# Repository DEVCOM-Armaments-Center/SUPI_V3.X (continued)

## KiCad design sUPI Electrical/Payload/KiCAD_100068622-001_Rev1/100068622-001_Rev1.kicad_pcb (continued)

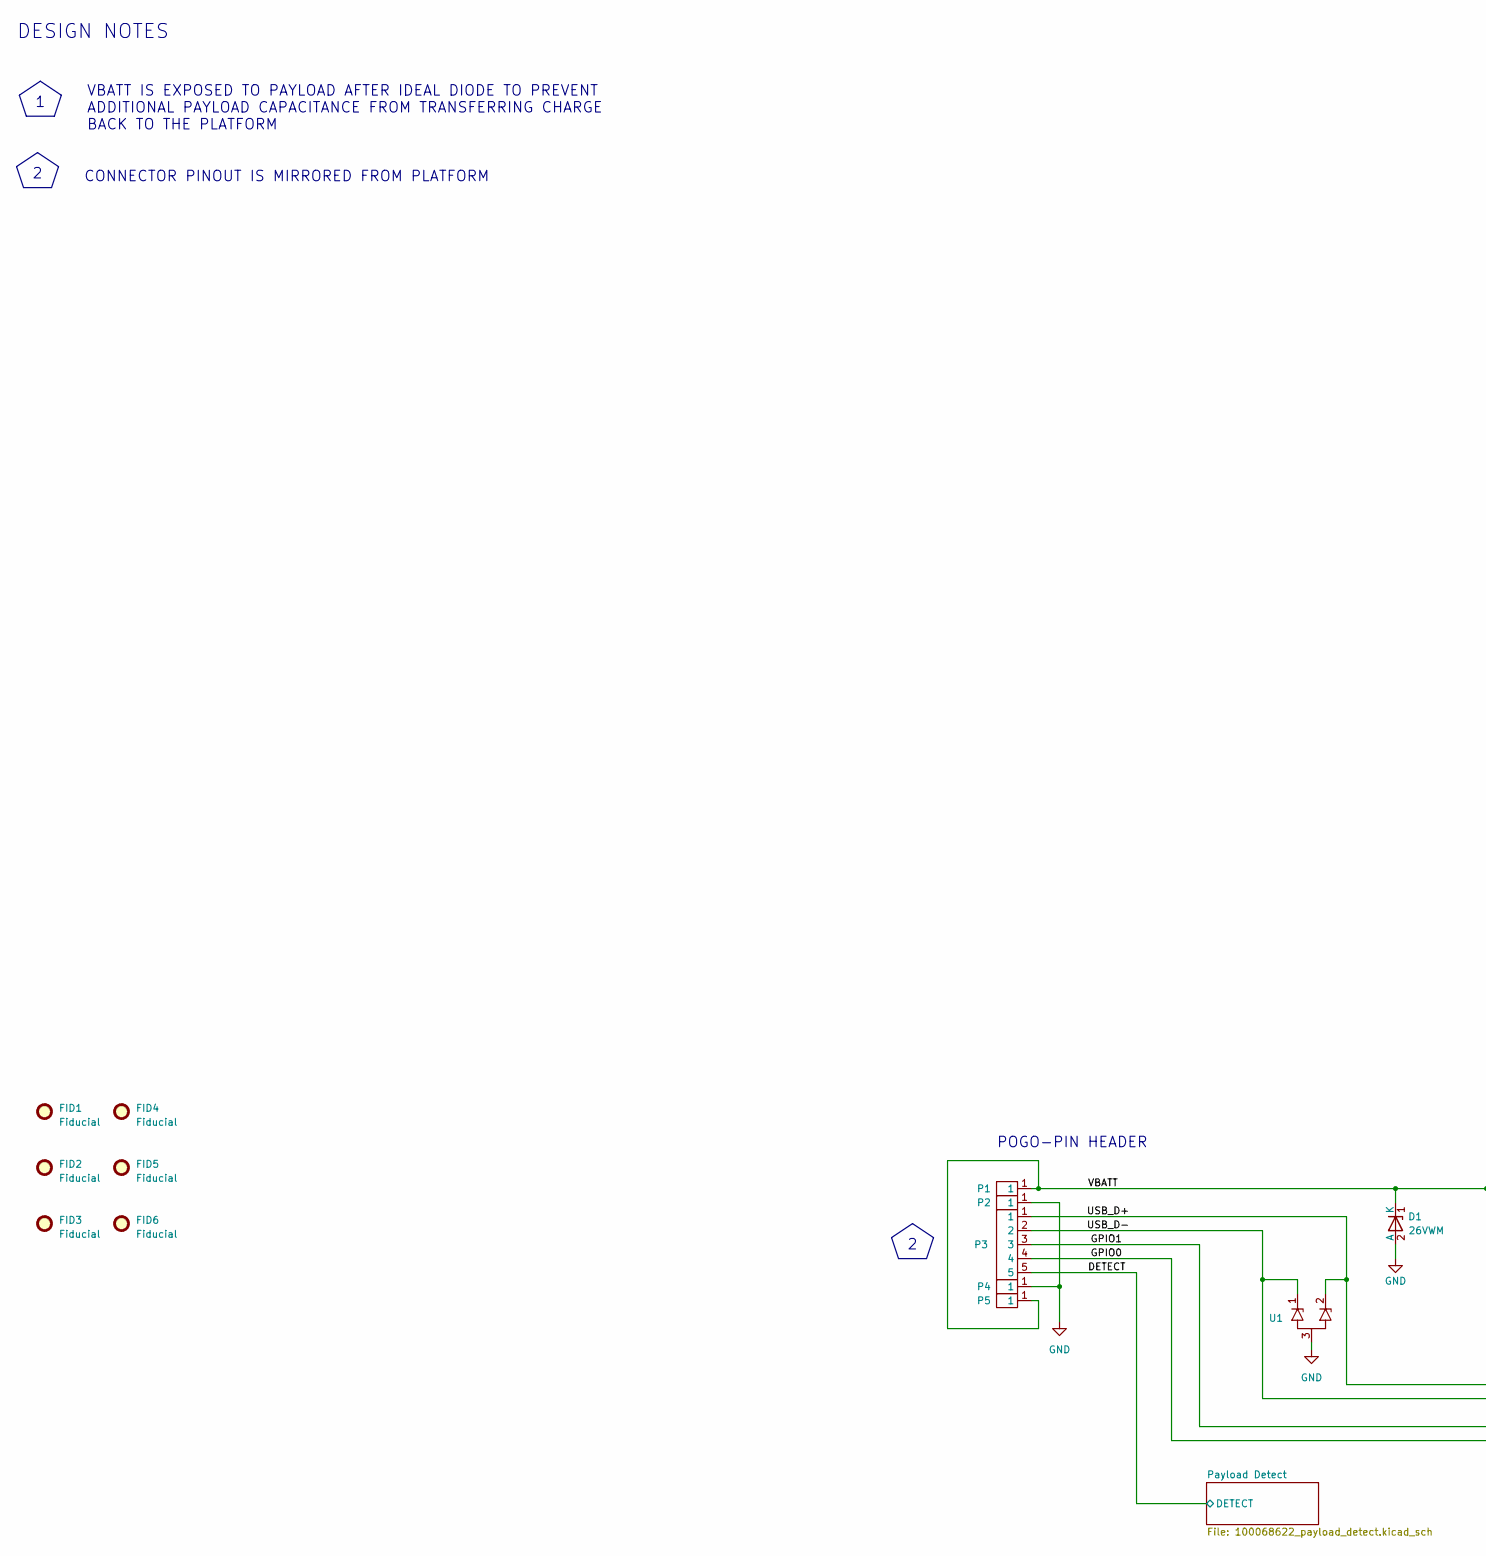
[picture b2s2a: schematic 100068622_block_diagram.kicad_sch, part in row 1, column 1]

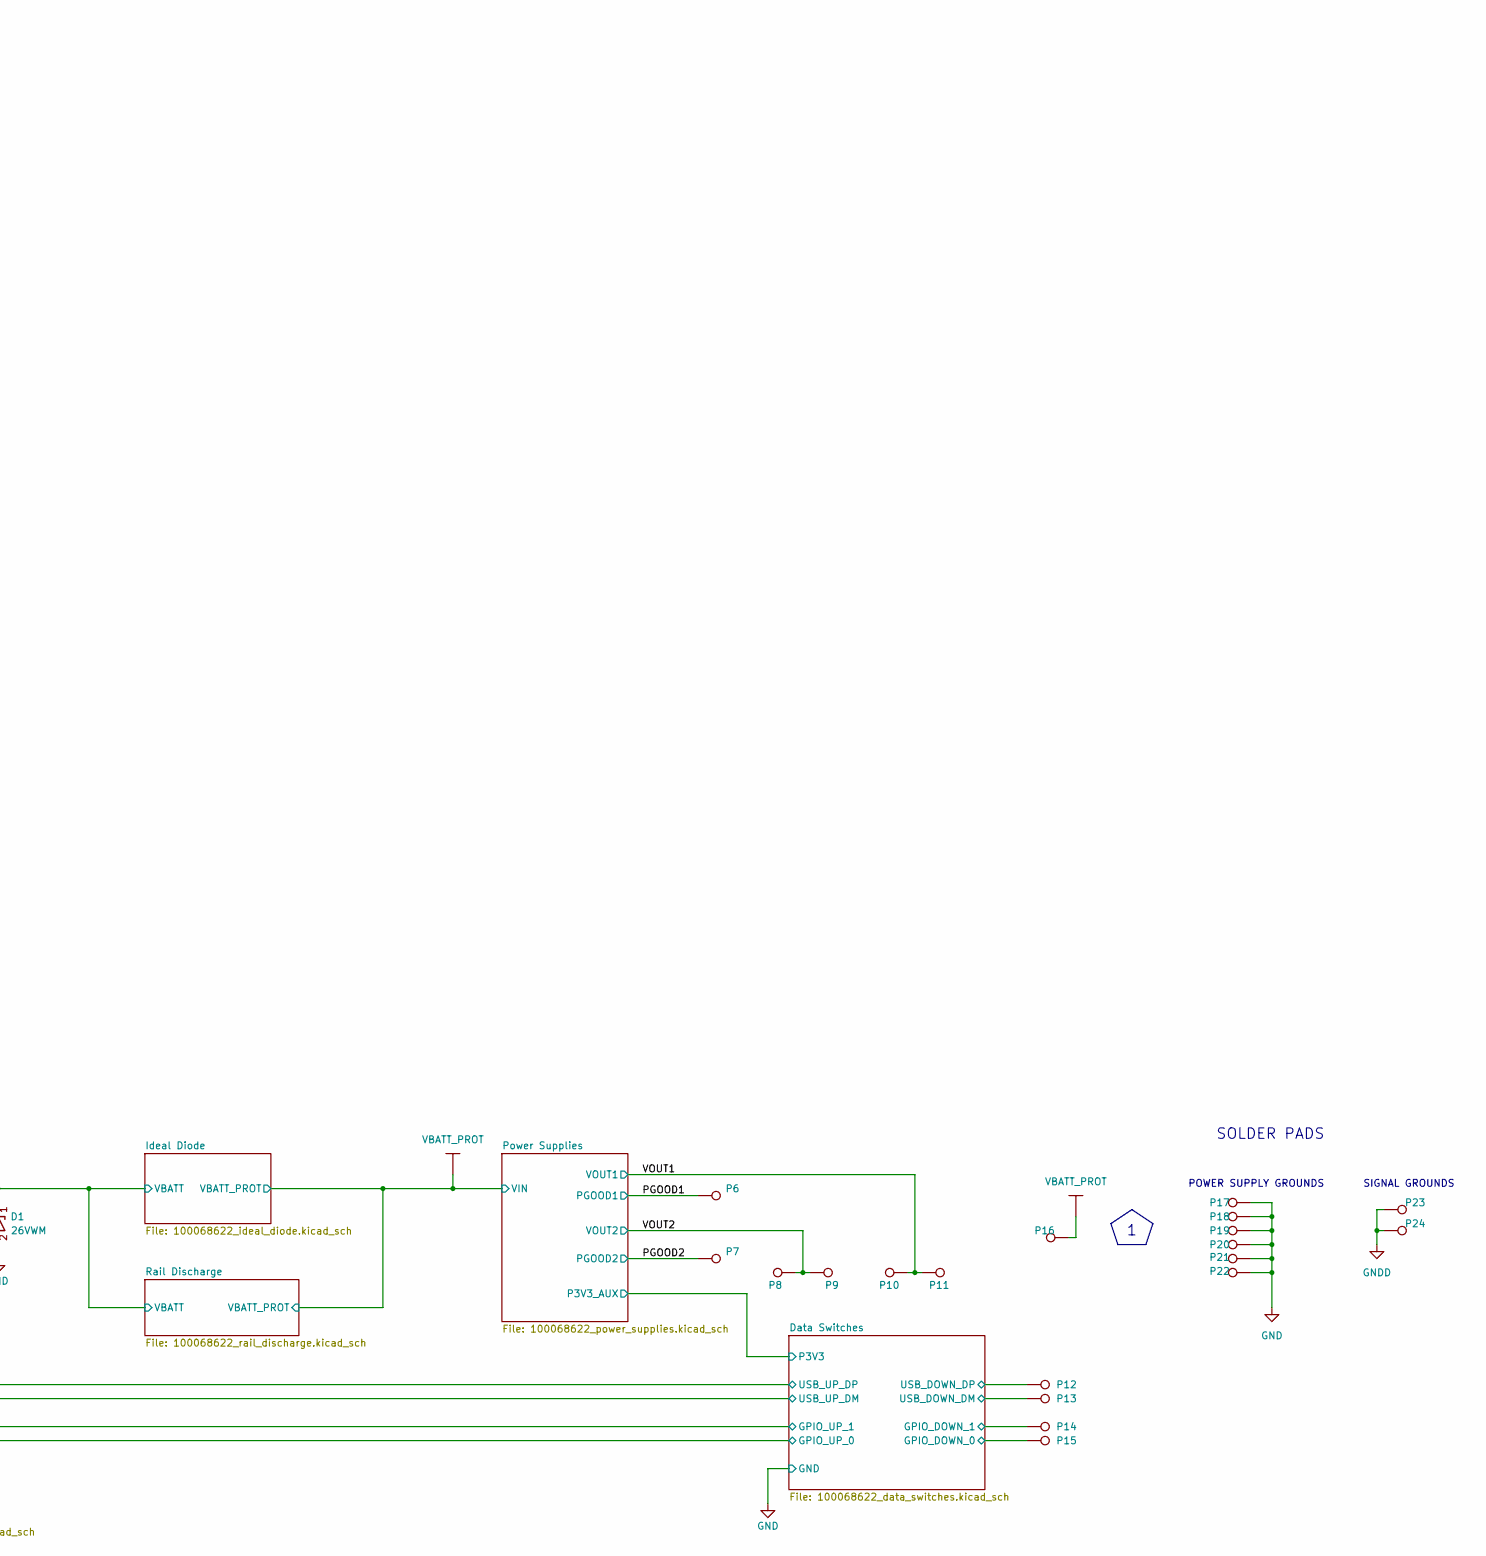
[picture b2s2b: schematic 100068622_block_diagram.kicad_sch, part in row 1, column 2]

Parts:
D1: 26VWM; SOD-123FL; MPN SMF26A
FID1, FID2, FID3, FID4, FID5, FID6: Fiducial; Fiducial_Cu0.040_Mask0.060
P1, P5: 829-22-001-20-001101; MPN 829-22-001-20-001101
P2, P4: 829-22-001-20-002101; MPN 829-22-001-20-002101
P3: 829-22-005-20-001101; MPN 829-22-005-20-001101
P6, P7, P8, P9, P10, P11, P12, P13, P14, P15, P17, P18, P19, P20, P21, P23, P24: Hand_Solder_Pad_100x80_mil
P16, P22: Hand_Solder_Pad_200x150_mil
U1: Diodes_DFN1006-3; MPN PESD5V0C2UM

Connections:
/Block Diagram/DETECT: P3.5; also elsewhere on the board
/Block Diagram/Data Switches/GPIO_DOWN_0: P15.1; also elsewhere on the board
/Block Diagram/Data Switches/GPIO_DOWN_1: P14.1; also elsewhere on the board
/Block Diagram/Data Switches/USB_DOWN_DM: P13.1; also elsewhere on the board
/Block Diagram/Data Switches/USB_DOWN_DP: P12.1; also elsewhere on the board
/Block Diagram/GPIO0: P3.4; also elsewhere on the board
/Block Diagram/GPIO1: P3.3; also elsewhere on the board
/Block Diagram/PGOOD1: P6.1; also elsewhere on the board
/Block Diagram/PGOOD2: P7.1; also elsewhere on the board
/Block Diagram/USB_D+: P3.1, U1.2 (K2); also elsewhere on the board
/Block Diagram/USB_D-: P3.2, U1.1 (K1); also elsewhere on the board
/Block Diagram/VBATT: D1.1 (K), P1.1, P5.1; also elsewhere on the board
/Block Diagram/VOUT1: P10.1, P11.1; also elsewhere on the board
/Block Diagram/VOUT2: P8.1, P9.1; also elsewhere on the board
GND: D1.2 (A), P2.1, P4.1, P17.1, P18.1, P19.1, P20.1, P21.1, P22.1, U1.3 (A); also elsewhere on the board
GNDD: P23.1, P24.1; also elsewhere on the board
VBATT_PROT: P16.1; also elsewhere on the board

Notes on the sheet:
CONNECTOR PINOUT IS MIRRORED FROM PLATFORM
POGO-PIN HEADER
SOLDER PADS
DESIGN NOTES
SIGNAL GROUNDS
POWER SUPPLY GROUNDS
VBATT IS EXPOSED TO PAYLOAD AFTER IDEAL DIODE TO PREVENT ADDITIONAL PAYLOAD CAPACITANCE FROM TRANSFERRING CHARGE BACK TO THE PLATFORM

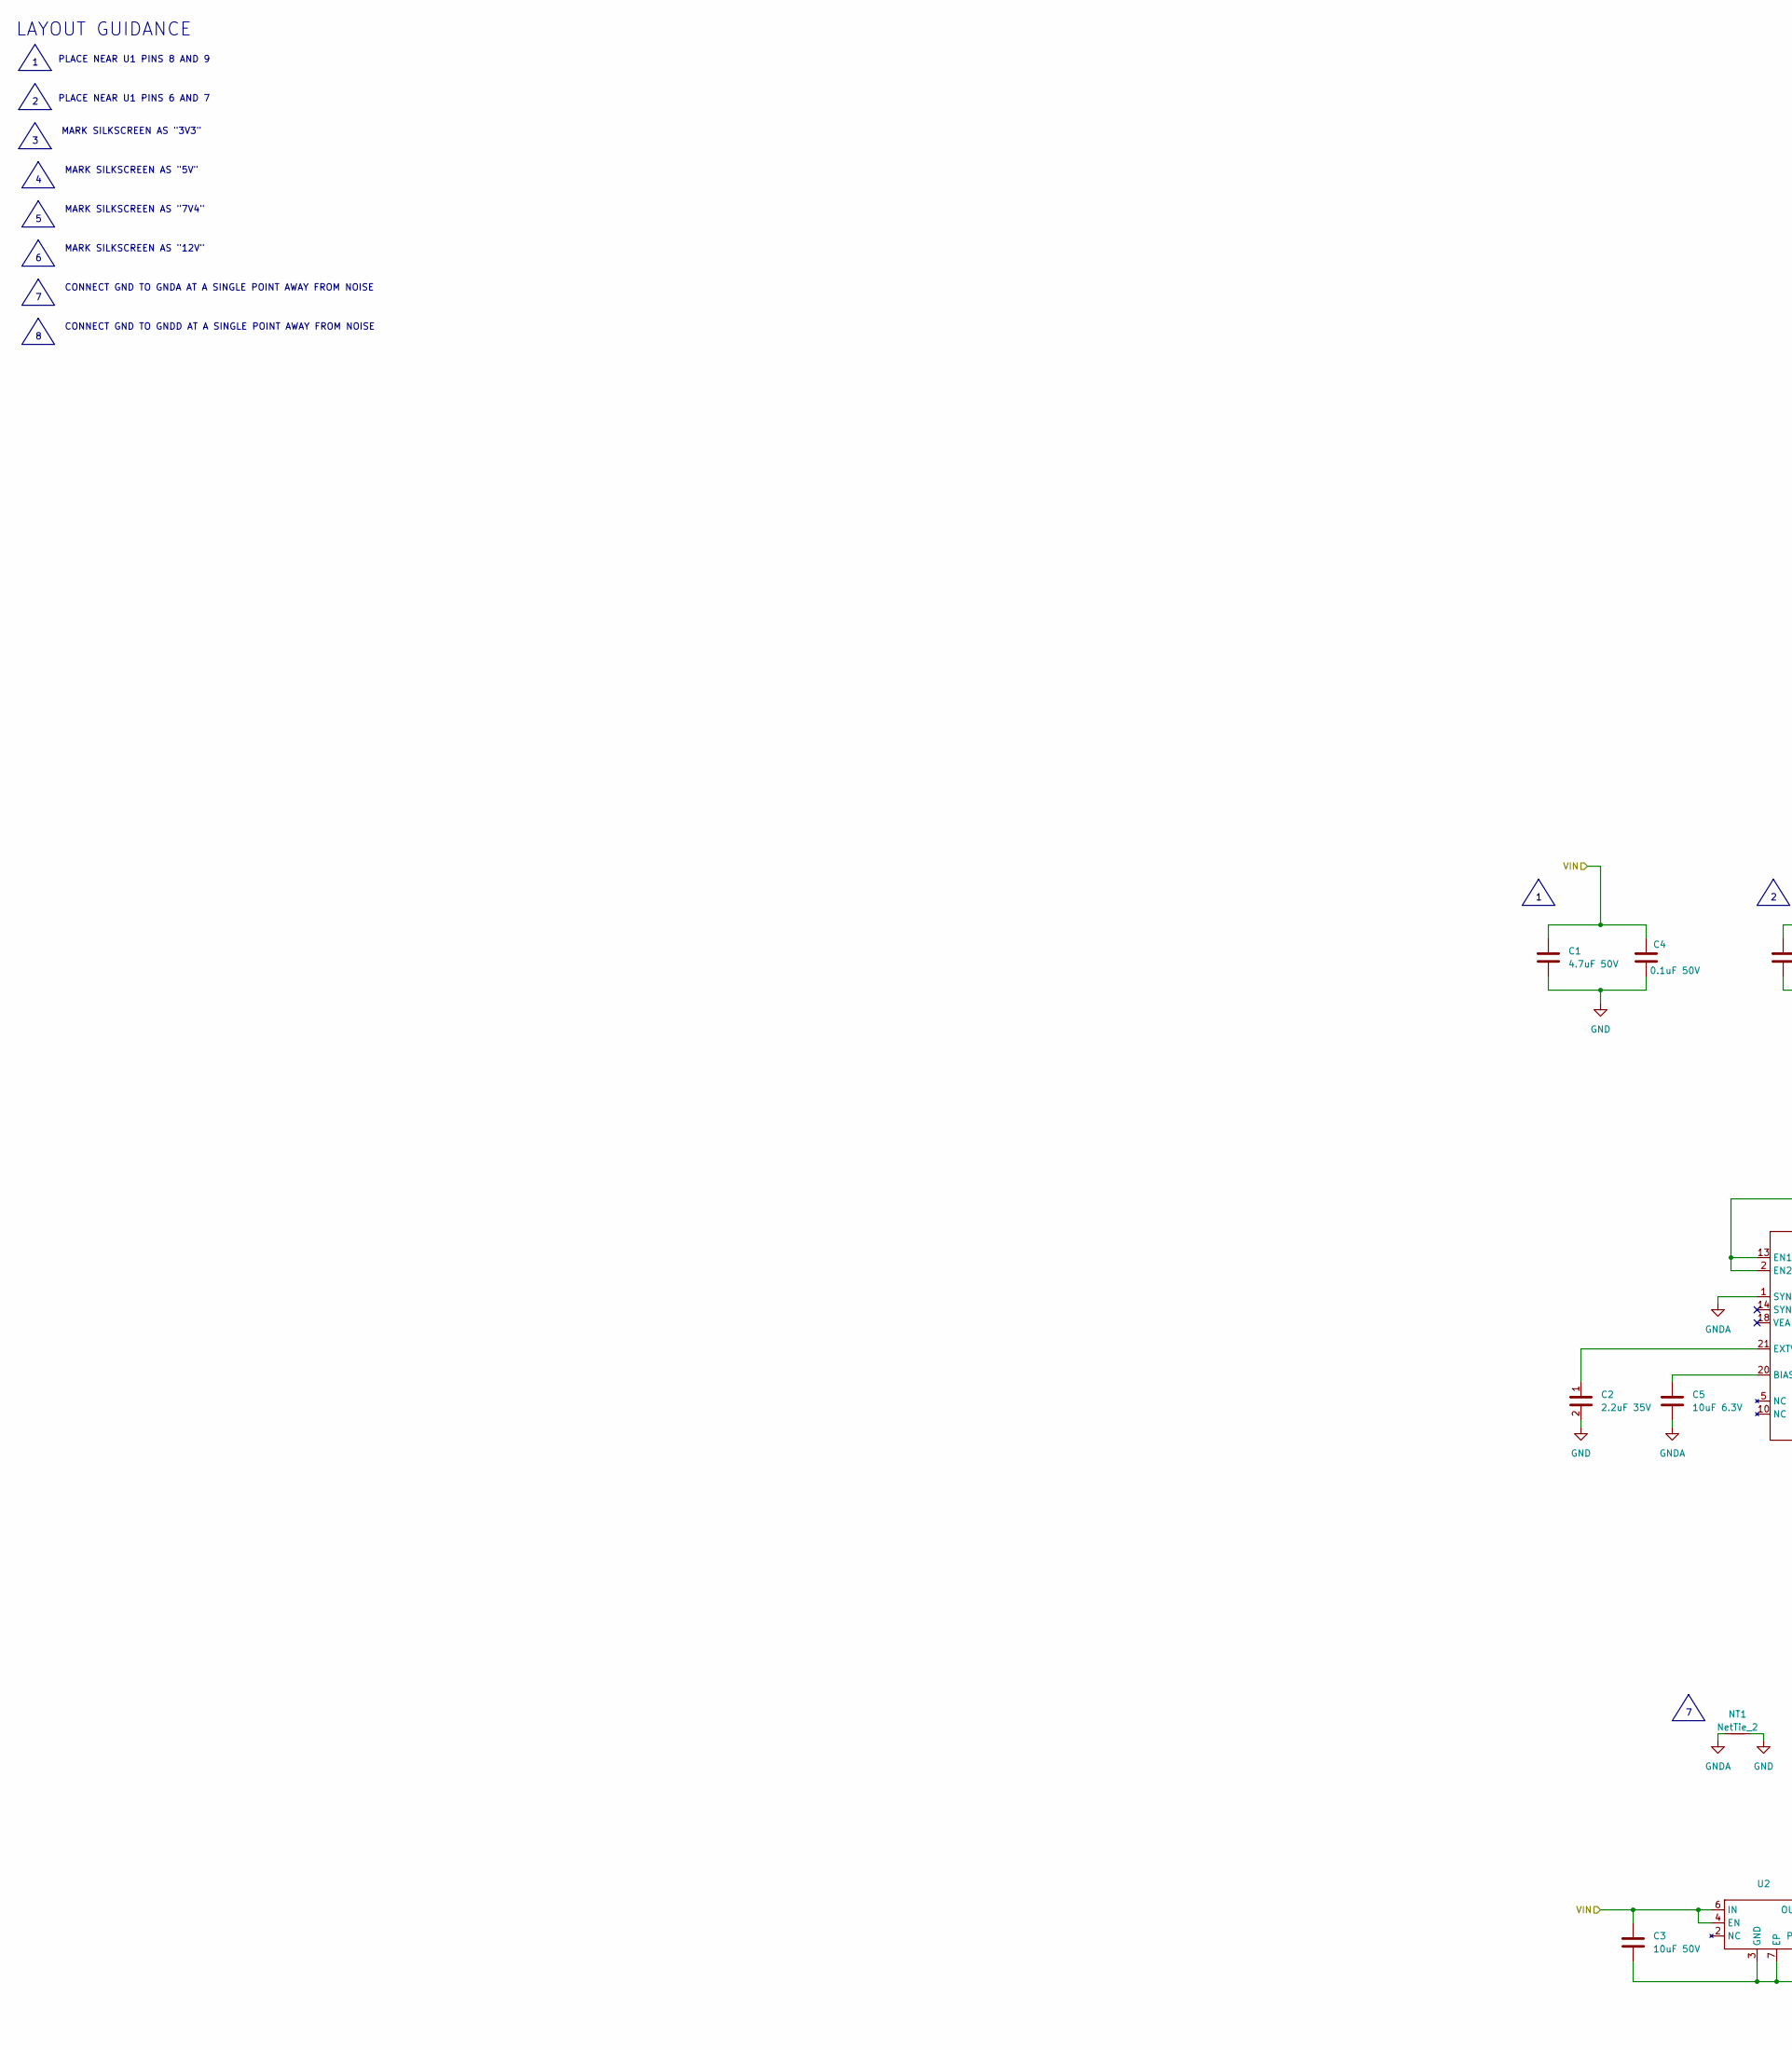
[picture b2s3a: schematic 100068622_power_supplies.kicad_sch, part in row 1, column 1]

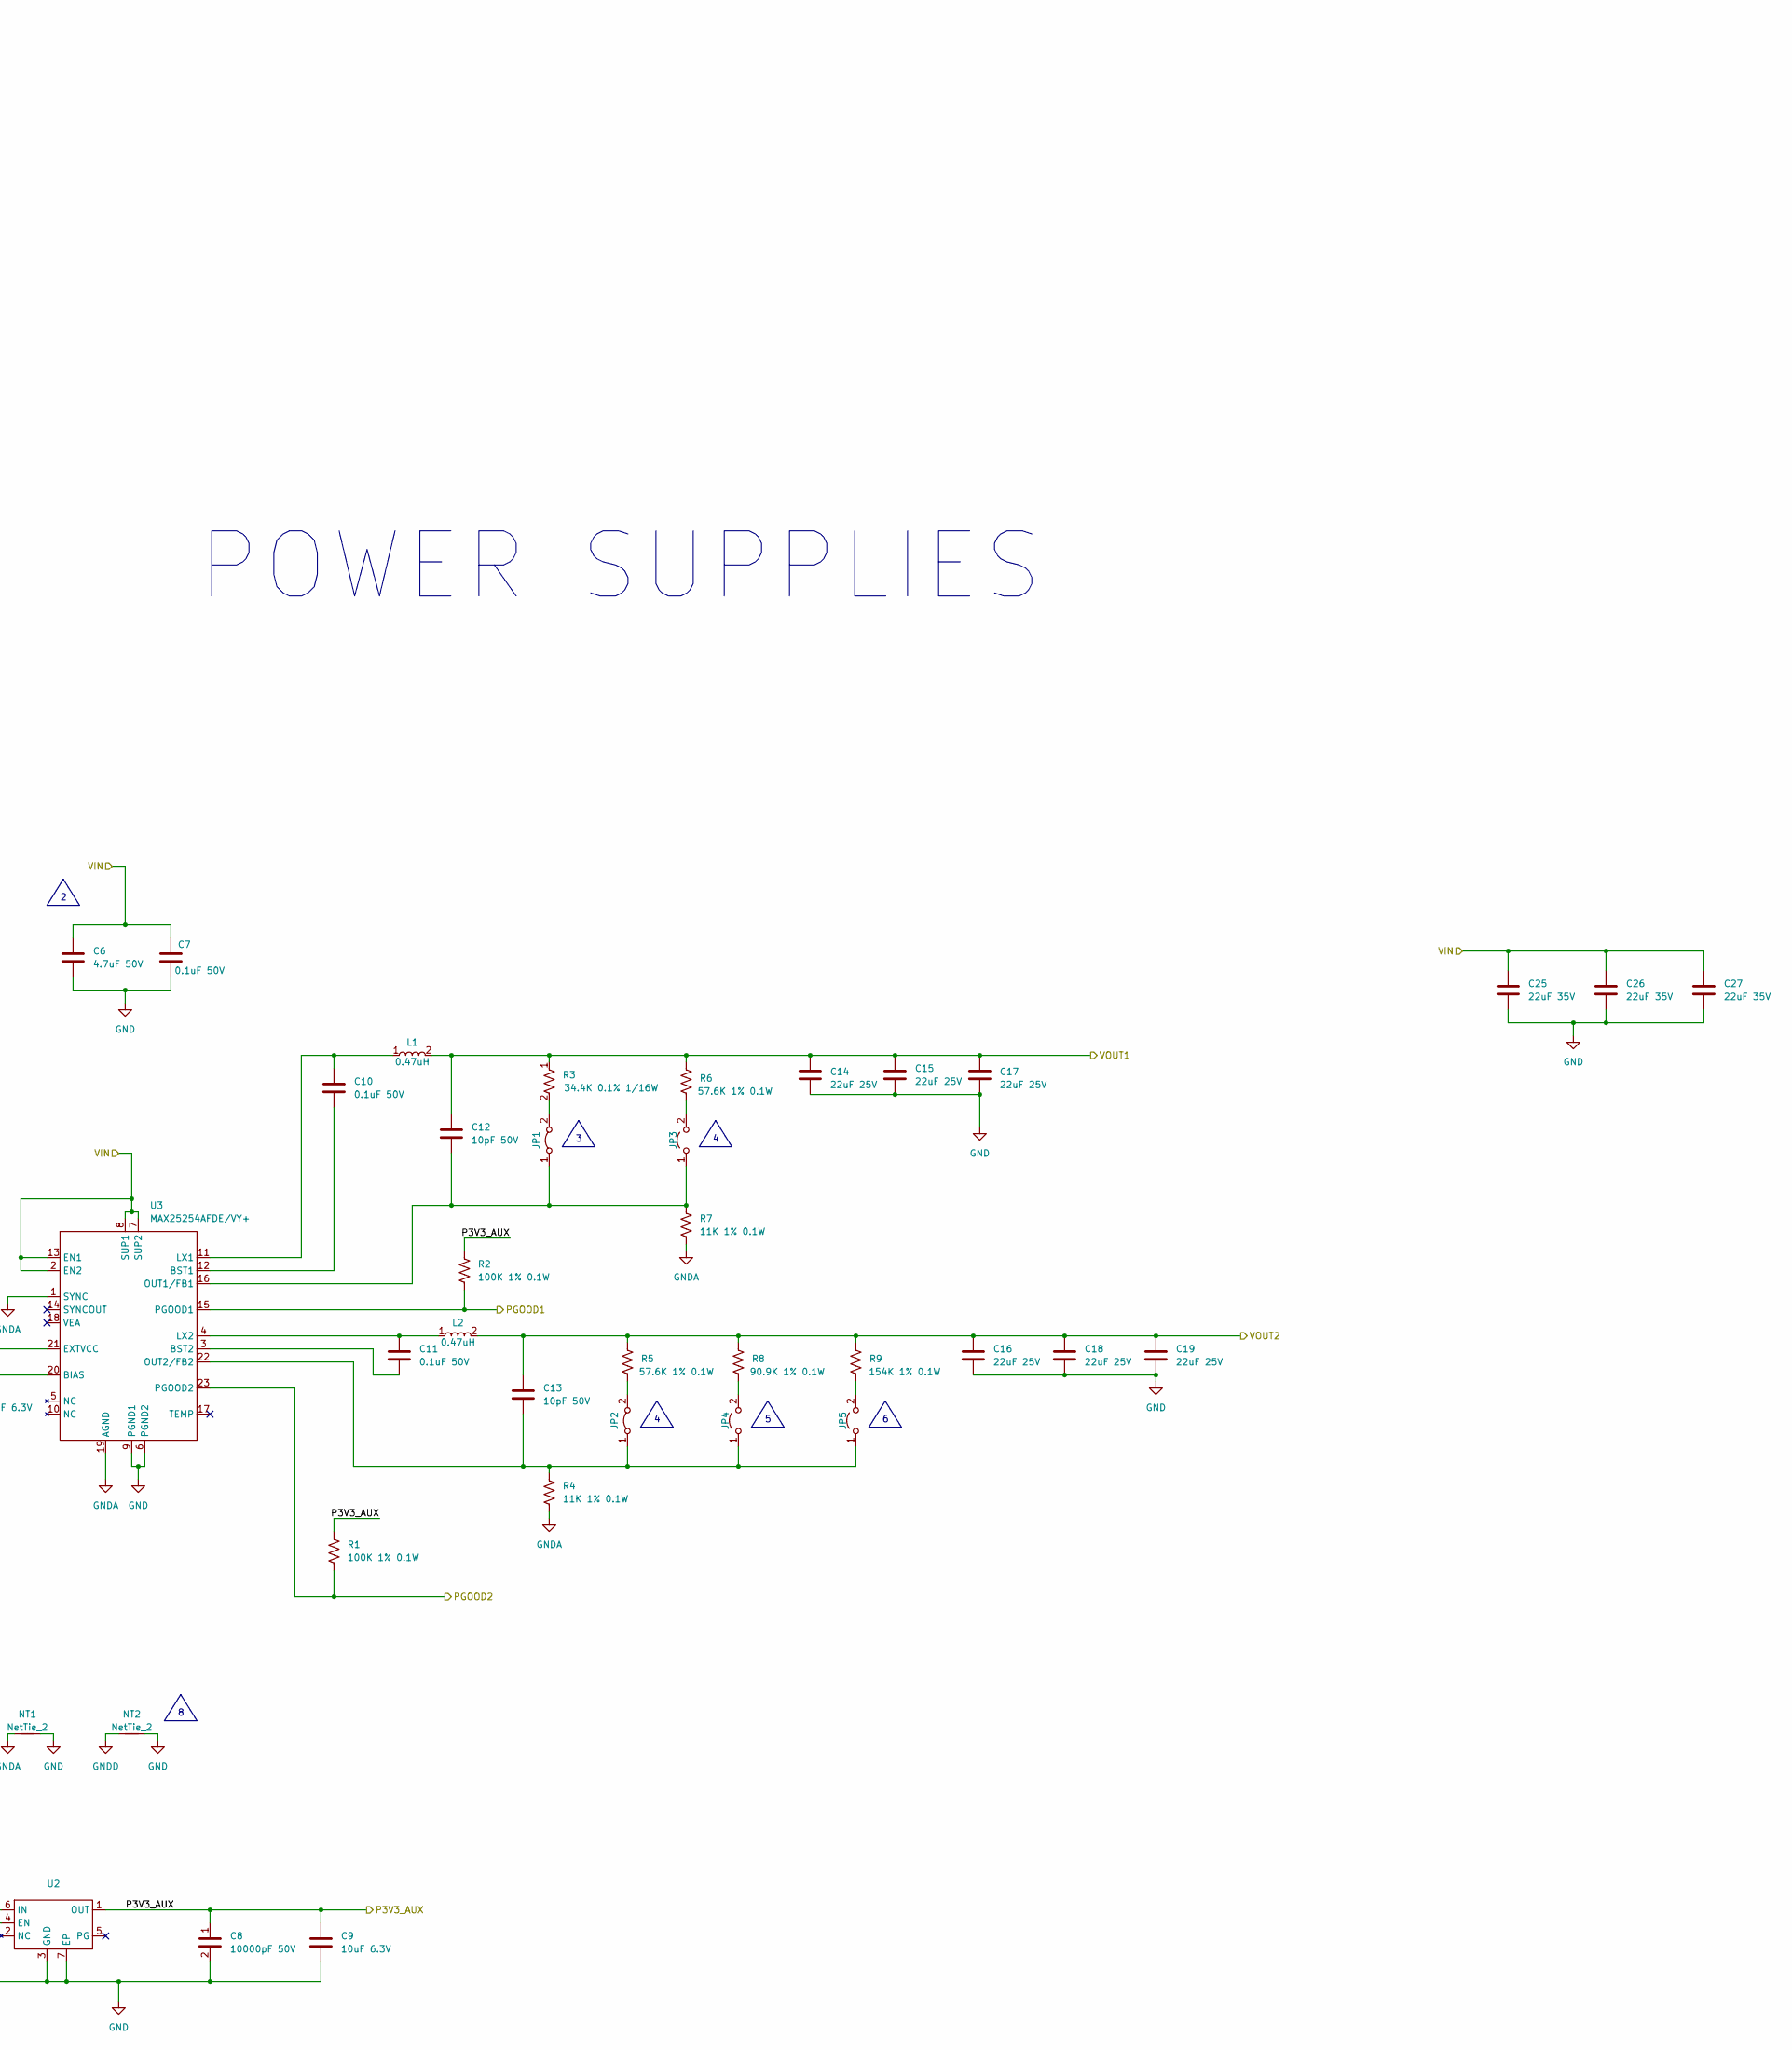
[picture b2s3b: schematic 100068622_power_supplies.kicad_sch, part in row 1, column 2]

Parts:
C1, C6: 4.7uF 50V; C_0805_2012Metric; MPN GRM21BZ71H475KE15L
C2: 2.2uF 35V; C_0402_1005Metric; MPN GRM155R6YA225KE11D
C3: 10uF 50V; C_0805_2012Metric; MPN GRM21BR61H106KE43L
C4, C7, C10, C11: 0.1uF 50V; C_0402_1005Metric; MPN GCM155R71H104ME02D
C5, C9: 10uF 6.3V; C_0402_1005Metric; MPN GRM155R60J106ME05D
C8: 10000pF 50V; C_0402_1005Metric; MPN GCM155R71H103KA55D
C12, C13: 10pF 50V; C_0402_1005Metric; MPN GCM1555C1H100FA16D
C14, C15, C16, C17, C18, C19: 22uF 25V; C_0805_2012Metric; MPN GRM21BR61E226ME44L
C25, C26, C27: 22uF 35V; C_0805_2012Metric; MPN C2012X5R1V226M125AC
JP1, JP2: Jumper_2_Bridged; SolderJumper-2_P1.3mm_Open_TrianglePad1.0x1.5mm
JP3, JP4, JP5: Jumper_2_Open; SolderJumper-2_P1.3mm_Open_TrianglePad1.0x1.5mm
L1, L2: 0.47uH; XEL4030-3.1mm; MPN XEL4030-471MEC
NT1, NT2: NetTie_2; NetTie segment - 10 mils horizontal
R1, R2: 100K 1% 0.1W; R_0402_1005Metric; MPN ERJ-2RKF1003X
R3: 34.4K 0.1% 1/16W; R_0402_1005Metric; MPN TNPW040234K4BEED
R4, R7: 11K 1% 0.1W; R_0402_1005Metric; MPN ERJ-U02F1102X
R5, R6: 57.6K 1% 0.1W; R_0402_1005Metric; MPN ERJ-2RKF5762X
R8: 90.9K 1% 0.1W; R_0402_1005Metric; MPN ERJ-2RKF9092X
R9: 154K 1% 0.1W; R_0402_1005Metric; MPN ERJ-2RKF1543X
U2: WDFN6_2x2_0.65p_1.72x1.12mm_EP; MPN NCP730BMT330TBG
U3: MAX25254AFDE/VY+; F234A5FY+1; MPN MAX25254AFDE/VY+

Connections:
/Block Diagram/PGOOD1: R2.2, U3.15 (PGOOD1); also elsewhere on the board
/Block Diagram/PGOOD2: R1.1, U3.23 (PGOOD2); also elsewhere on the board
/Block Diagram/Power Supplies/P3V3_AUX: C8.1, C9.1, R1.2, R2.1, U2.1 (OUT); also elsewhere on the board
/Block Diagram/VOUT1: C12.1, C14.1, C15.1, C17.1, L1.2, R3.1, R6.1; also elsewhere on the board
/Block Diagram/VOUT2: C13.1, C16.1, C18.1, C19.1, L2.2, R5.1, R8.1, R9.1; also elsewhere on the board
GND: C1.2, C2.2, C3.2, C4.2, C6.2, C7.2, C8.2, C9.2, C14.2, C15.2, C16.2, C17.2, C18.2, C19.2, C25.2, C26.2, C27.2, NT1.2, NT2.2, U2.3 (GND), U2.7 (EP), U3.6 (PGND2), U3.9 (PGND1); also elsewhere on the board
GNDA: C5.2, NT1.1, R4.2, R7.2, U3.1 (SYNC), U3.19 (AGND)
GNDD: NT2.1; also elsewhere on the board
unnamed: C12.2, JP1.1 (A), JP3.1 (A), R7.1, U3.16 (OUT1/FB1)
unnamed: JP1.2 (B), R3.2
unnamed: C13.2, JP2.1 (A), JP4.1 (A), JP5.1 (A), R4.1, U3.22 (OUT2/FB2)
unnamed: JP2.2 (B), R5.2
unnamed: JP3.2 (B), R6.2
unnamed: JP4.2 (B), R8.2
unnamed: JP5.2 (B), R9.2
unnamed: C5.1, U3.20 (BIAS)
unnamed: C10.2, U3.12 (BST1)
unnamed: C11.2, U3.3 (BST2)
unnamed: C2.1, U3.21 (EXTVCC)
unnamed: C10.1, L1.1, U3.11 (LX1)
unnamed: C11.1, L2.1, U3.4 (LX2)
VBATT_PROT: C1.1, C3.1, C4.1, C6.1, C7.1, C25.1, C26.1, C27.1, U2.4 (EN), U2.6 (IN), U3.2 (EN2), U3.7 (SUP2), U3.8 (SUP1), U3.13 (EN1); also elsewhere on the board

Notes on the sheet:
MARK SILKSCREEN AS "3V3"
PLACE NEAR U1 PINS 8 AND 9
CONNECT GND TO GNDA AT A SINGLE POINT AWAY FROM NOISE
MARK SILKSCREEN AS "5V"
CONNECT GND TO GNDD AT A SINGLE POINT AWAY FROM NOISE
PLACE NEAR U1 PINS 6 AND 7
POWER SUPPLIES
LAYOUT GUIDANCE
MARK SILKSCREEN AS "7V4"
MARK SILKSCREEN AS "12V"

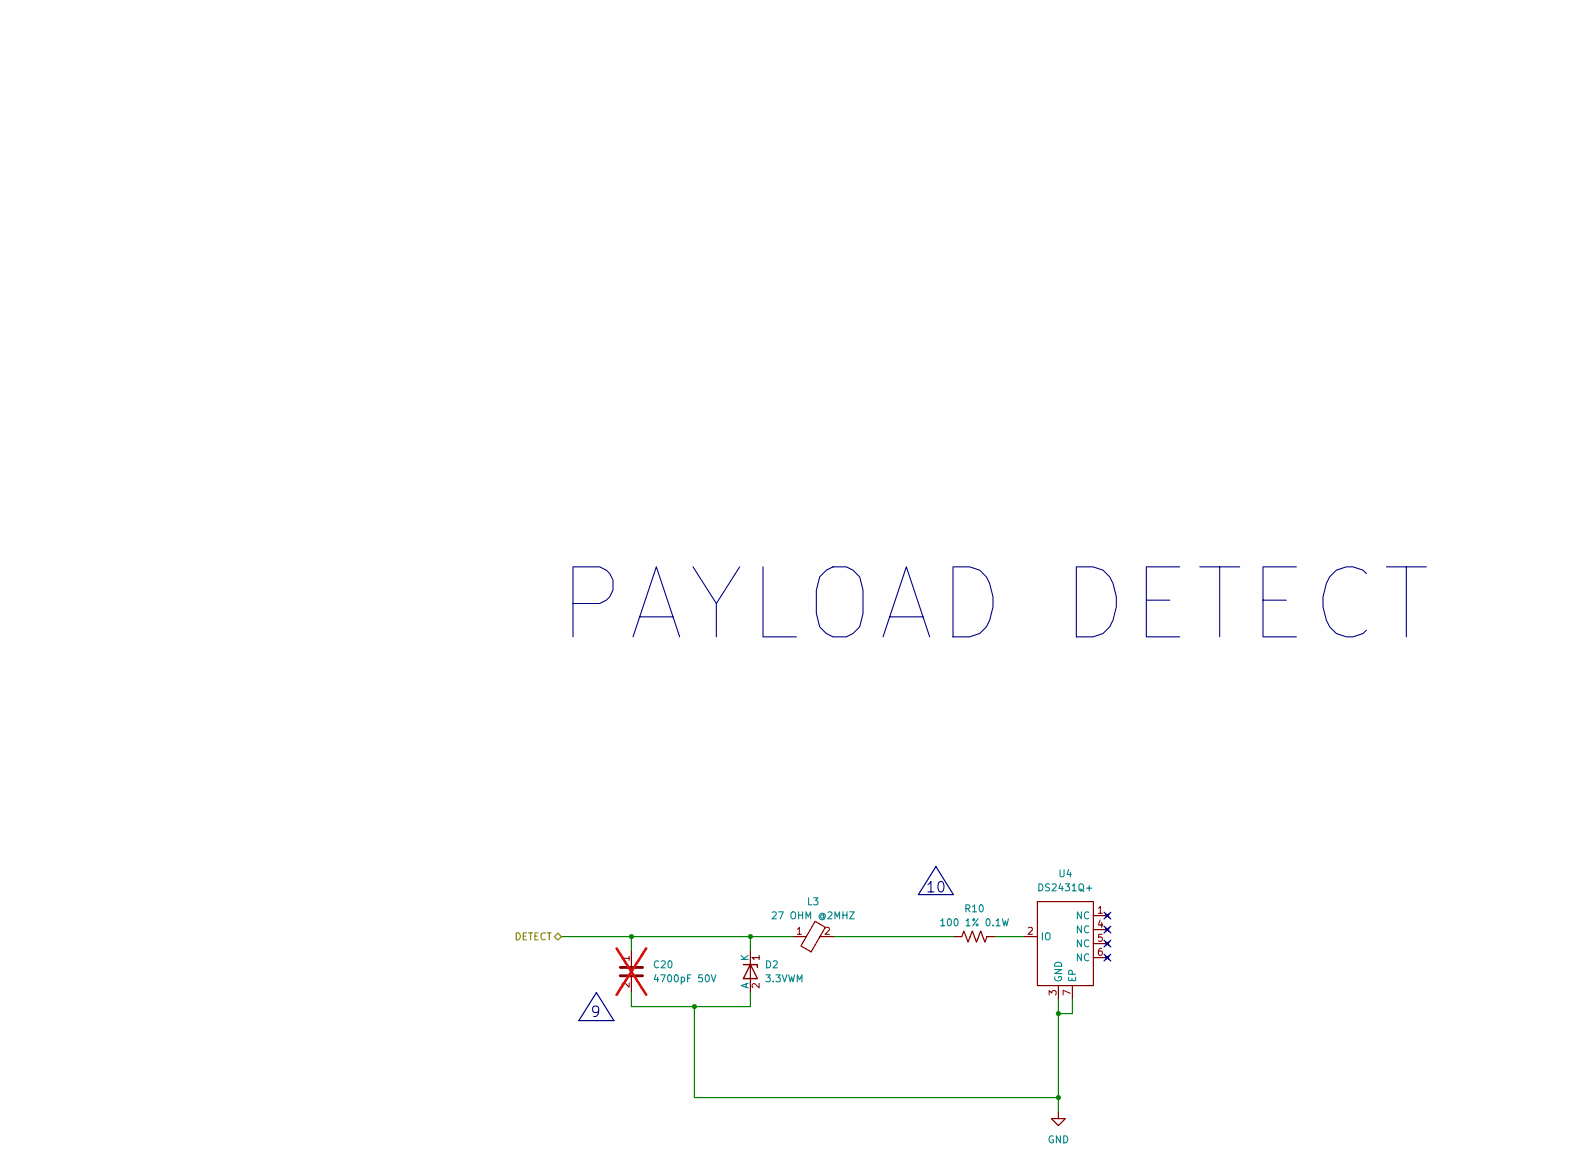
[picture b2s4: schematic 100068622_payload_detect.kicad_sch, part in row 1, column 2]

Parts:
C20: 4700pF 50V; C_0402_1005Metric; MPN GCM155R71H472KA37J; not fitted
D2: 3.3VWM; SOD-123FL; MPN SMF3.3
L3: 27 OHM @2MHZ; 0806 SMD; MPN MDF2016BSS270C
R10: 100 1% 0.1W; R_0402_1005Metric; MPN ERJ-2RKF1000X
U4: DS2431Q+; Maxim_TDFN-6-1EP_3x3mm_P0.95mm_EP1.5x2.3mm; MPN DS2431Q+T&R

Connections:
/Block Diagram/DETECT: C20.1, D2.1 (K), L3.1; also elsewhere on the board
GND: C20.2, D2.2 (A), U4.3 (GND), U4.7 (EP); also elsewhere on the board
unnamed: L3.2, R10.2
unnamed: R10.1, U4.2 (IO)

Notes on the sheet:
PLACE R8 NEXT TO U2
LAYOUT GUIDANCE
PAYLOAD DETECT
PLACE C26 AND D1 NEXT TO P12

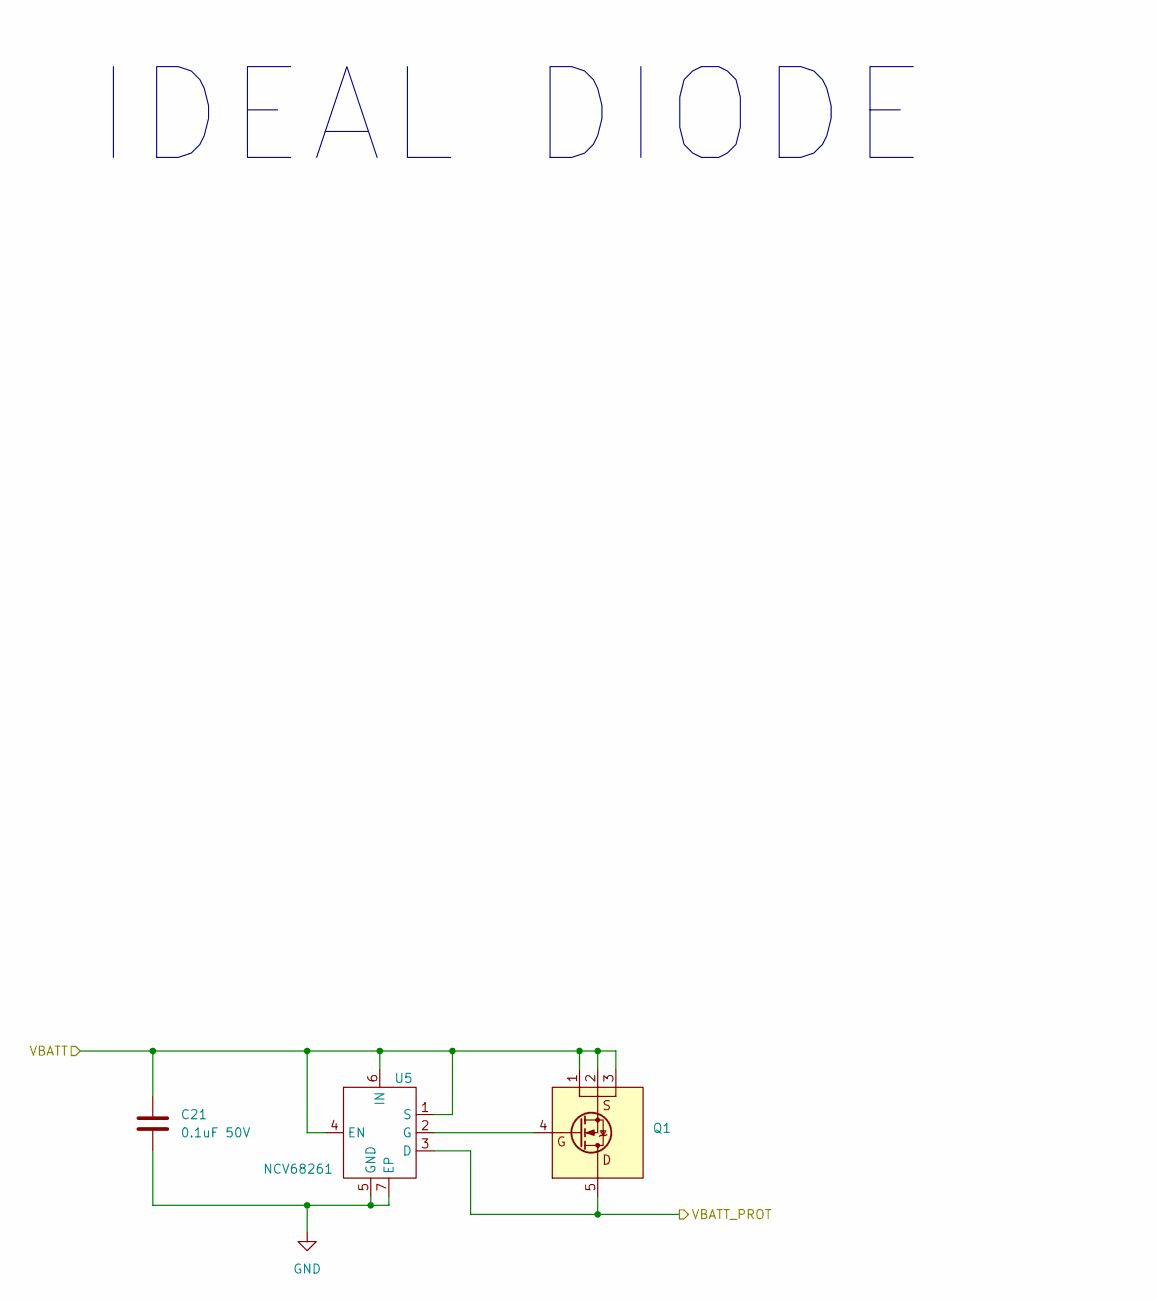
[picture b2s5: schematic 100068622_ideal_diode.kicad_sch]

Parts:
C21: 0.1uF 50V; C_0402_1005Metric; MPN GCM155R71H104ME02D
Q1: NTTFS2D1N04HL; WDFN8_3.3_x_3.3_0.65mm_p; MPN NTTFS2D1N04HLTWG
U5: NCV68261; WDFNW6_2x2_0.65p_EP; MPN NCV68261MTWAITBG

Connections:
/Block Diagram/VBATT: C21.1, Q1.1 (S), Q1.2 (S), Q1.3 (S), U5.1 (S), U5.4 (EN), U5.6 (IN); also elsewhere on the board
GND: C21.2, U5.5 (GND), U5.7 (EP); also elsewhere on the board
unnamed: Q1.4 (G), U5.2 (G)
VBATT_PROT: Q1.5 (D), U5.3 (D); also elsewhere on the board

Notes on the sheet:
IDEAL DIODE

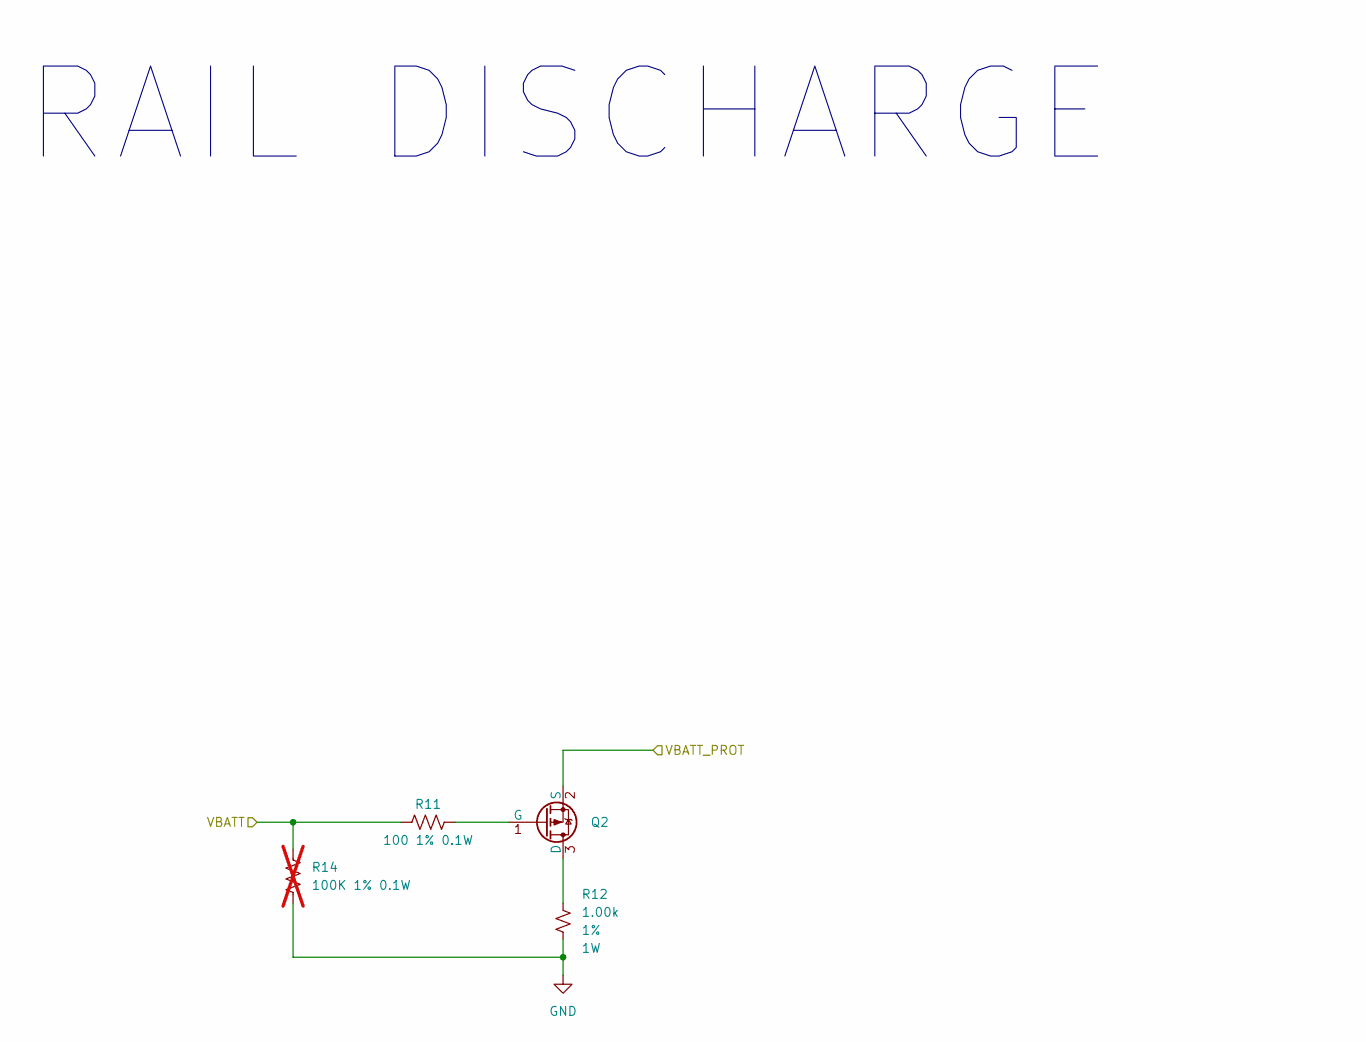
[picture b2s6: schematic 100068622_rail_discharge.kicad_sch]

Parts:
Q2: SOT-23; MPN DMP610DL-13
R11: 100 1% 0.1W; R_0402_1005Metric; MPN ERJ-2RKF1000X
R12: 1.00k; R_2512_HandSoldering; Tolerance 1%; MPN RMCF2512FT1K00
R14: 100K 1% 0.1W; R_0402_1005Metric; MPN ERJ-2RKF1003X; not fitted

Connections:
/Block Diagram/VBATT: R11.1, R14.1; also elsewhere on the board
GND: R12.1, R14.2; also elsewhere on the board
unnamed: Q2.3 (D), R12.2
unnamed: Q2.1 (G), R11.2
VBATT_PROT: Q2.2 (S); also elsewhere on the board

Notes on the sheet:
RAIL DISCHARGE
